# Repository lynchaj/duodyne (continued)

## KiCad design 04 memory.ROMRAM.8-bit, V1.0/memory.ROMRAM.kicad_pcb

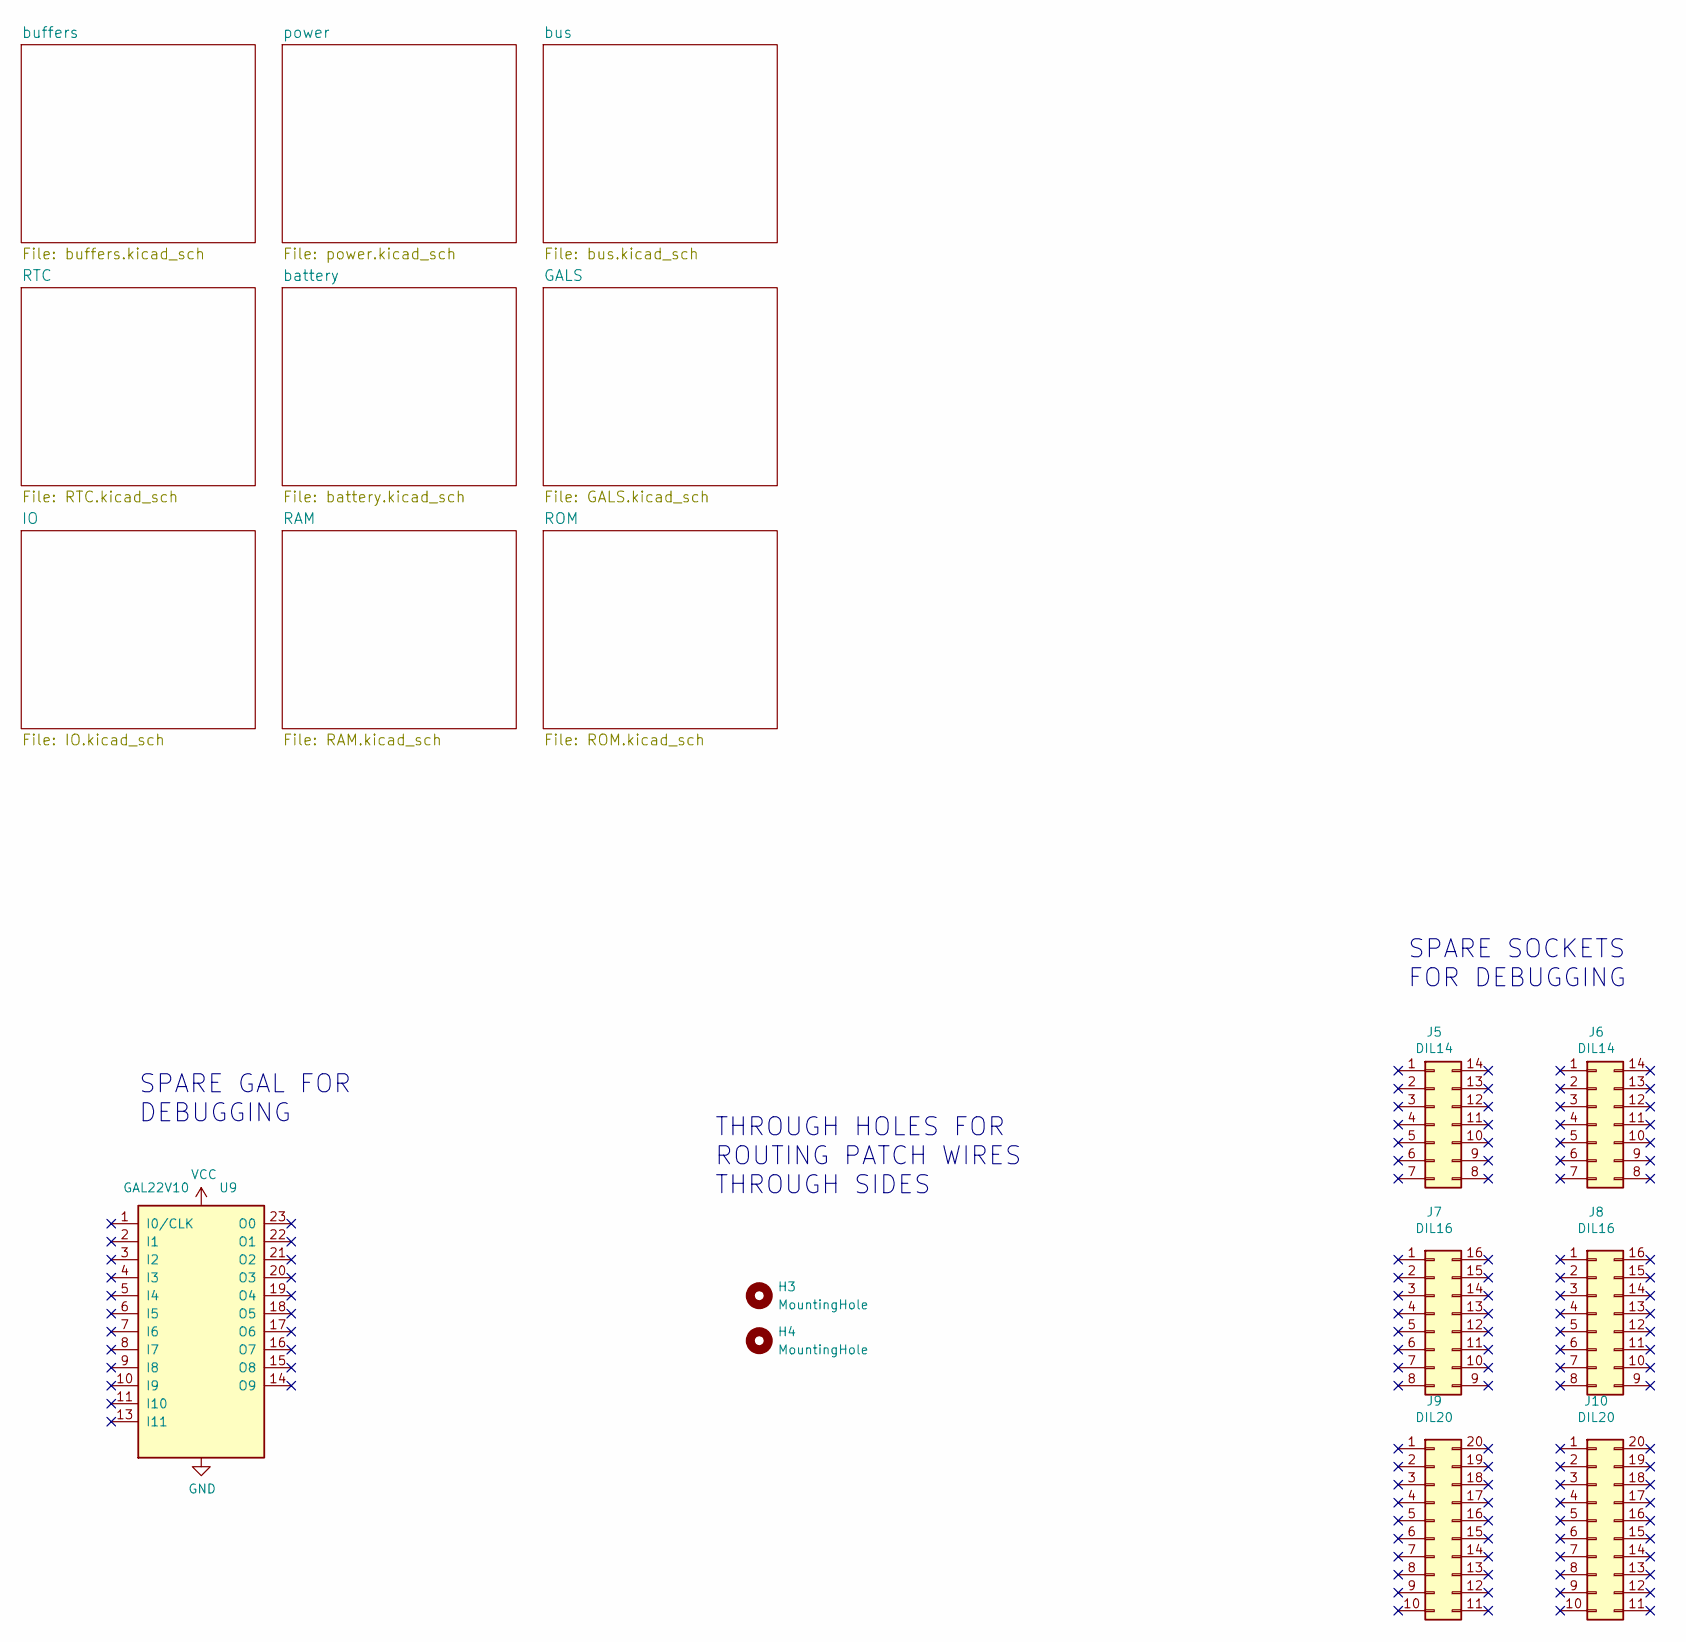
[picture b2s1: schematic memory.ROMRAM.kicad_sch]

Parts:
H3, H4: MountingHole; MountingHole_2.1mm
J5, J6: DIL14; DIP-14_W7.62mm
J7, J8: DIL16; DIP-16_W7.62mm
J9, J10: DIL20; DIP-20_W7.62mm
U9: GAL22V10; DIP-24_W7.62mm

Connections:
GND: U9.12 (GND); also elsewhere on the board
VCC: U9.24 (VCC); also elsewhere on the board

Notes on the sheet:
SPARE SOCKETS FOR DEBUGGING
SPARE GAL FOR DEBUGGING
THROUGH HOLES FOR ROUTING PATCH WIRES THROUGH SIDES

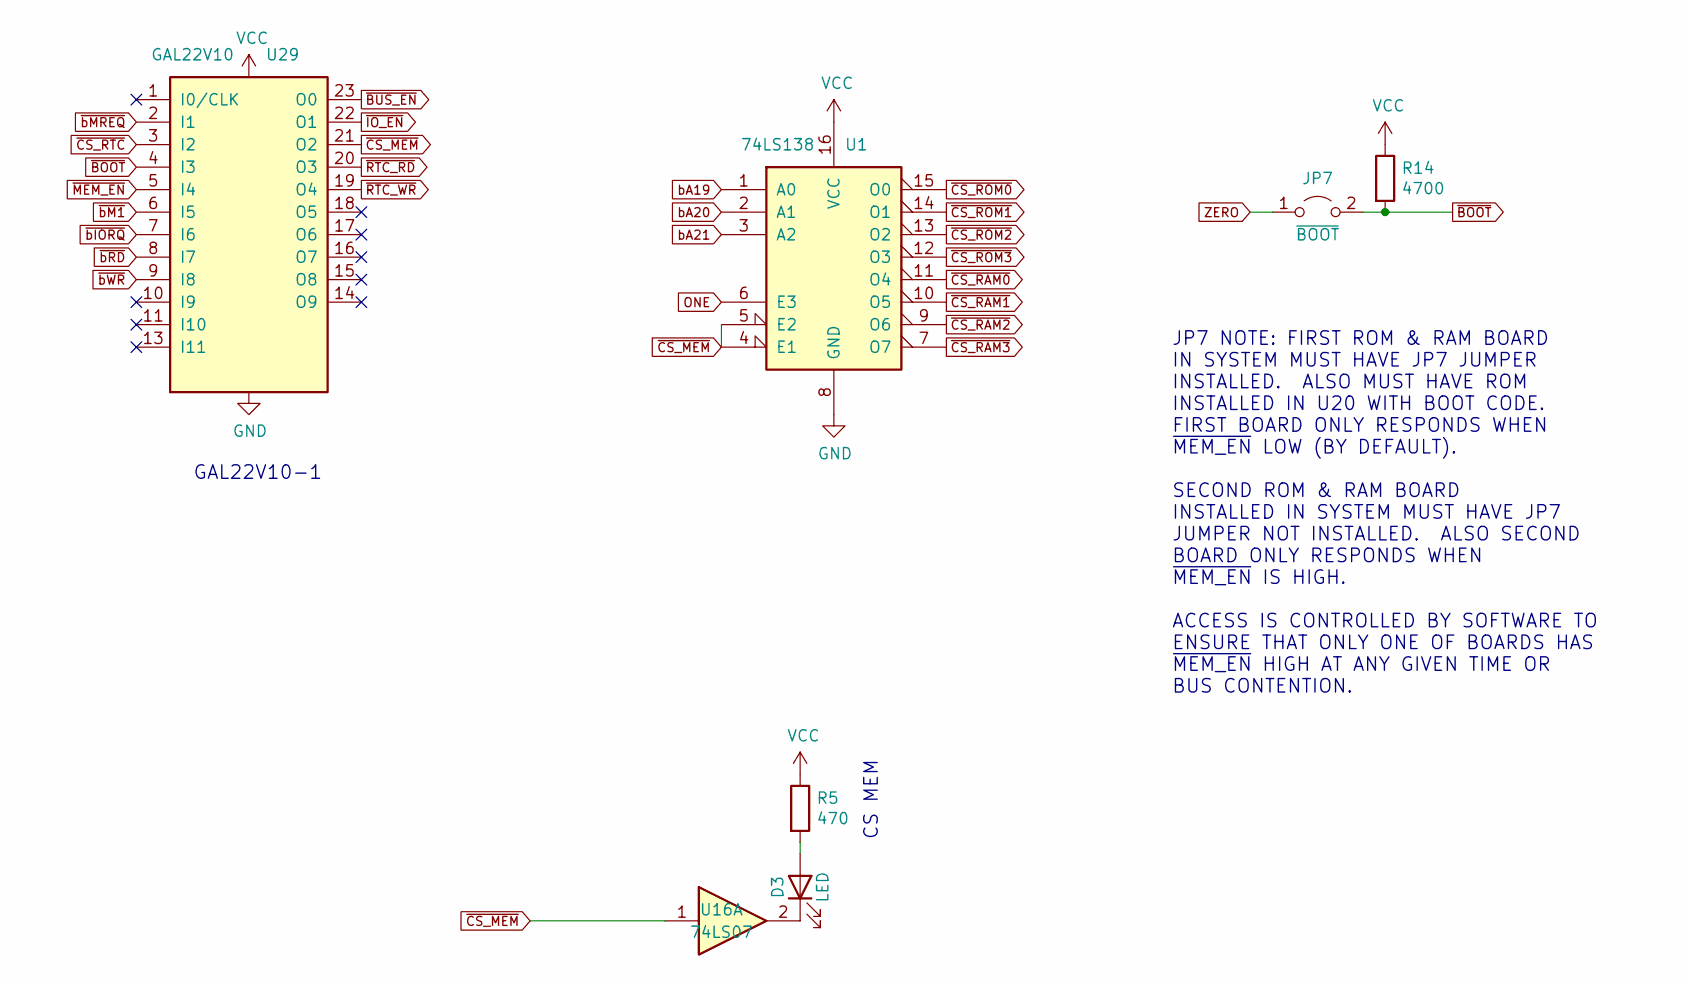
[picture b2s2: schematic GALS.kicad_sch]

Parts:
D3: LED; LED_D3.0mm_Horizontal_O3.81mm_Z2.0mm
JP7: ~{BOOT}; PinHeader_1x02_P2.54mm_Horizontal
R5: 470; R_Axial_DIN0207_L6.3mm_D2.5mm_P7.62mm_Horizontal
R14: 4700; R_Axial_DIN0207_L6.3mm_D2.5mm_P7.62mm_Horizontal
U1: 74LS138; DIP-16_W7.62mm
U16: 74LS07; DIP-14_W7.62mm
U29: GAL22V10; DIP-24_W7.62mm

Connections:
GND: U1.8 (GND), U29.12 (GND); also elsewhere on the board
unnamed: D3.1 (K), U16.2
unnamed: D3.2 (A), R5.2
ONE: U1.6 (E3); also elsewhere on the board
VCC: R5.1, R14.1, U1.16 (VCC), U29.24 (VCC); also elsewhere on the board
ZERO: JP7.1 (A); also elsewhere on the board
bA19: U1.1 (A0); also elsewhere on the board
bA20: U1.2 (A1); also elsewhere on the board
bA21: U1.3 (A2); also elsewhere on the board
~BOOT: JP7.2 (B), R14.2, U29.4 (I3)
~BUS_EN: U29.23 (O0); also elsewhere on the board
~CS_MEM: U1.4 (E1), U1.5 (E2), U16.1, U29.21 (O2)
~CS_RAM0: U1.11 (O4); also elsewhere on the board
~CS_RAM1: U1.10 (O5); also elsewhere on the board
~CS_RAM2: U1.9 (O6); also elsewhere on the board
~CS_RAM3: U1.7 (O7); also elsewhere on the board
~CS_ROM0: U1.15 (O0); also elsewhere on the board
~CS_ROM1: U1.14 (O1); also elsewhere on the board
~CS_ROM2: U1.13 (O2); also elsewhere on the board
~CS_ROM3: U1.12 (O3); also elsewhere on the board
~CS_RTC: U29.3 (I2); also elsewhere on the board
~IO_EN: U29.22 (O1); also elsewhere on the board
~MEM_EN: U29.5 (I4); also elsewhere on the board
~RTC_RD: U29.20 (O3); also elsewhere on the board
~RTC_WR: U29.19 (O4); also elsewhere on the board
~bIORQ: U29.7 (I6); also elsewhere on the board
~bM1: U29.6 (I5); also elsewhere on the board
~bMREQ: U29.2 (I1); also elsewhere on the board
~bRD: U29.8 (I7); also elsewhere on the board
~bWR: U29.9 (I8); also elsewhere on the board

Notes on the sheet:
GAL22V10-1
JP7 NOTE: FIRST ROM & RAM BOARD IN SYSTEM MUST HAVE JP7 JUMPER INSTALLED. ALSO MUST HAVE ROM INSTALLED IN U20 WITH BOOT CODE. FIRST BOARD ONLY RESPONDS WHEN ~{MEM_EN} LOW (BY DEFAULT). SECOND ROM & RAM BOARD INSTALLED IN SYSTEM MUST HAVE JP7 JUMPER NOT INSTALLED. ALSO SECOND BOARD ONLY RESPONDS WHE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
CS MEM

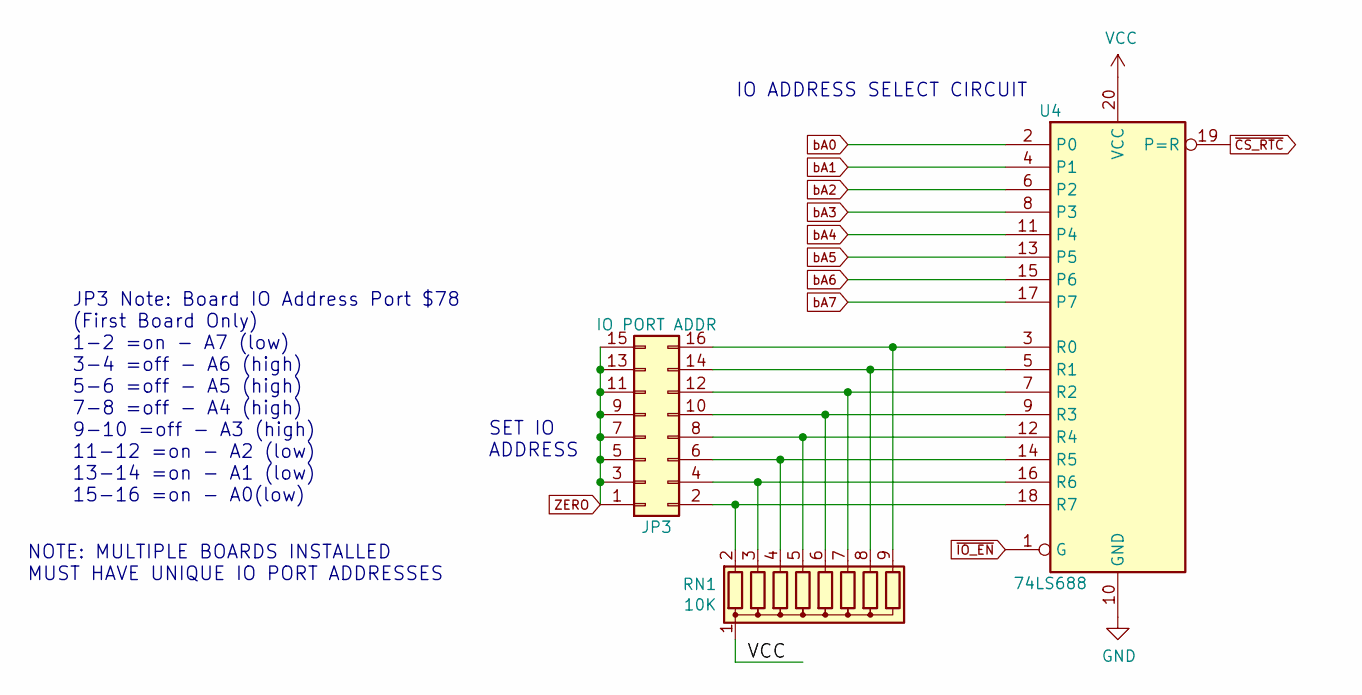
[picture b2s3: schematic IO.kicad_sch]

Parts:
JP3: IO PORT ADDR; PinHeader_2x08_P2.54mm_Vertical
RN1: 10K; R_Array_SIP9
U4: 74LS688; DIP-20_W7.62mm

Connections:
GND: U4.10 (GND); also elsewhere on the board
unnamed: JP3.2, RN1.2 (R1), U4.18 (R7)
unnamed: JP3.4, RN1.3 (R2), U4.16 (R6)
unnamed: JP3.6, RN1.4 (R3), U4.14 (R5)
unnamed: JP3.8, RN1.5 (R4), U4.12 (R4)
unnamed: JP3.10, RN1.6 (R5), U4.9 (R3)
unnamed: JP3.12, RN1.7 (R6), U4.7 (R2)
unnamed: JP3.14, RN1.8 (R7), U4.5 (R1)
unnamed: JP3.16, RN1.9 (R8), U4.3 (R0)
VCC: RN1.1 (common), U4.20 (VCC); also elsewhere on the board
ZERO: JP3.1, JP3.3, JP3.5, JP3.7, JP3.9, JP3.11, JP3.13, JP3.15; also elsewhere on the board
bA0: U4.2 (P0); also elsewhere on the board
bA1: U4.4 (P1); also elsewhere on the board
bA2: U4.6 (P2); also elsewhere on the board
bA3: U4.8 (P3); also elsewhere on the board
bA4: U4.11 (P4); also elsewhere on the board
bA5: U4.13 (P5); also elsewhere on the board
bA6: U4.15 (P6); also elsewhere on the board
bA7: U4.17 (P7); also elsewhere on the board
~CS_RTC: U4.19 (P=R); also elsewhere on the board
~IO_EN: U4.1 (G); also elsewhere on the board

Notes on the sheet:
JP3 Note: Board IO Address Port $78 (First Board Only) 1-2 =on - A7 (low) 3-4 =off - A6 (high) 5-6 =off - A5 (high) 7-8 =off - A4 (high) 9-10 =off - A3 (high) 11-12 =on - A2 (low) 13-14 =on - A1 (low) 15-16 =on - A0(low)
NOTE: MULTIPLE BOARDS INSTALLED MUST HAVE UNIQUE IO PORT ADDRESSES
IO ADDRESS SELECT CIRCUIT
SET IO ADDRESS

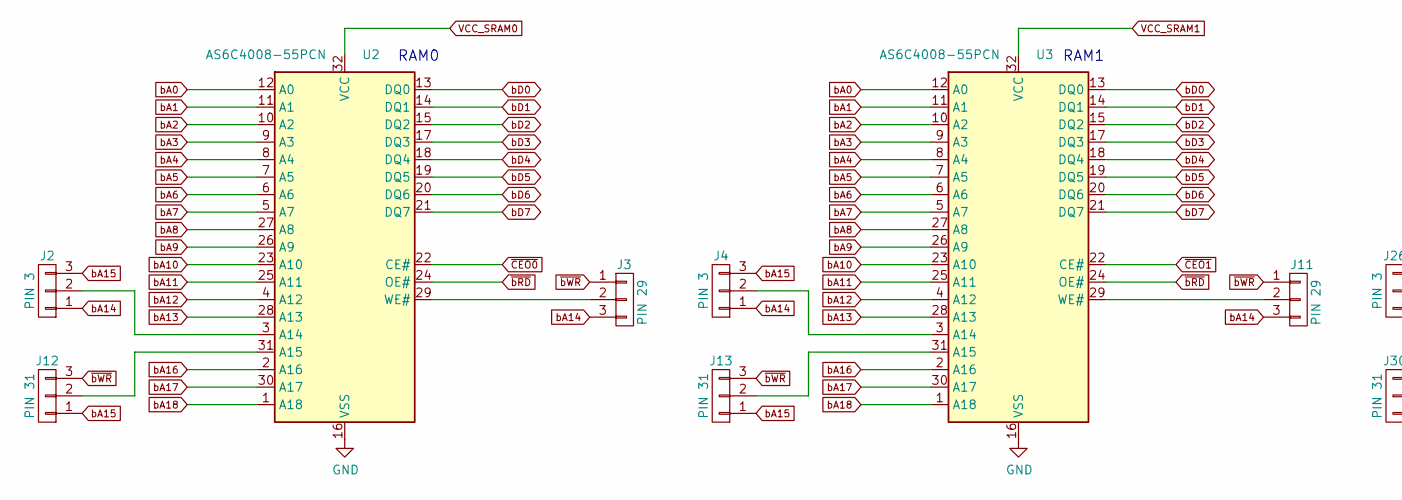
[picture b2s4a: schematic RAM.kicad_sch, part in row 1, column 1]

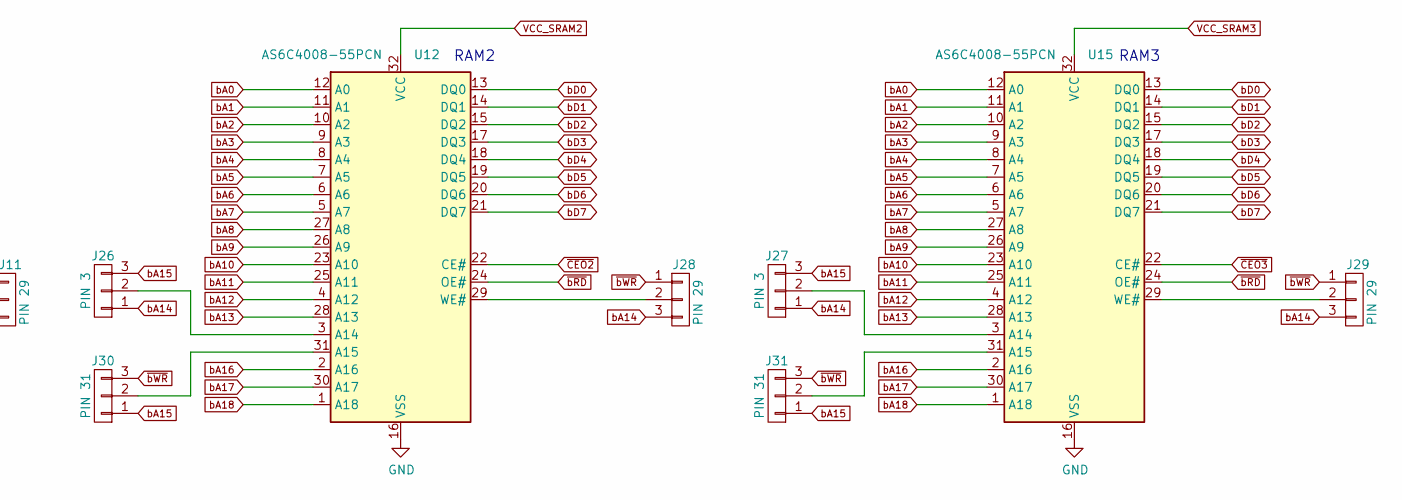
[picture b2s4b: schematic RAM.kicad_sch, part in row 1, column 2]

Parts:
J2, J4, J26, J27: PIN 3; PinHeader_1x03_P2.54mm_Vertical
J3, J11, J28, J29: PIN 29; PinHeader_1x03_P2.54mm_Vertical
J12, J13, J30, J31: PIN 31; PinHeader_1x03_P2.54mm_Vertical
U2, U3, U12, U15: AS6C4008-55PCN; DIP-32_W15.24mm

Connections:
GND: U2.16 (VSS), U3.16 (VSS), U12.16 (VSS), U15.16 (VSS); also elsewhere on the board
unnamed: J2.2, U2.3 (A14)
unnamed: J3.2, U2.29 (WE#)
unnamed: J4.2, U3.3 (A14)
unnamed: J11.2, U3.29 (WE#)
unnamed: J12.2, U2.31 (A15)
unnamed: J13.2, U3.31 (A15)
unnamed: J26.2, U12.3 (A14)
unnamed: J27.2, U15.3 (A14)
unnamed: J28.2, U12.29 (WE#)
unnamed: J29.2, U15.29 (WE#)
unnamed: J30.2, U12.31 (A15)
unnamed: J31.2, U15.31 (A15)
VCC_SRAM0: U2.32 (VCC); also elsewhere on the board
VCC_SRAM1: U3.32 (VCC); also elsewhere on the board
VCC_SRAM2: U12.32 (VCC); also elsewhere on the board
VCC_SRAM3: U15.32 (VCC); also elsewhere on the board
bA0: U2.12 (A0), U3.12 (A0), U12.12 (A0), U15.12 (A0); also elsewhere on the board
bA1: U2.11 (A1), U3.11 (A1), U12.11 (A1), U15.11 (A1); also elsewhere on the board
bA2: U2.10 (A2), U3.10 (A2), U12.10 (A2), U15.10 (A2); also elsewhere on the board
bA3: U2.9 (A3), U3.9 (A3), U12.9 (A3), U15.9 (A3); also elsewhere on the board
bA4: U2.8 (A4), U3.8 (A4), U12.8 (A4), U15.8 (A4); also elsewhere on the board
bA5: U2.7 (A5), U3.7 (A5), U12.7 (A5), U15.7 (A5); also elsewhere on the board
bA6: U2.6 (A6), U3.6 (A6), U12.6 (A6), U15.6 (A6); also elsewhere on the board
bA7: U2.5 (A7), U3.5 (A7), U12.5 (A7), U15.5 (A7); also elsewhere on the board
bA8: U2.27 (A8), U3.27 (A8), U12.27 (A8), U15.27 (A8); also elsewhere on the board
bA9: U2.26 (A9), U3.26 (A9), U12.26 (A9), U15.26 (A9); also elsewhere on the board
bA10: U2.23 (A10), U3.23 (A10), U12.23 (A10), U15.23 (A10); also elsewhere on the board
bA11: U2.25 (A11), U3.25 (A11), U12.25 (A11), U15.25 (A11); also elsewhere on the board
bA12: U2.4 (A12), U3.4 (A12), U12.4 (A12), U15.4 (A12); also elsewhere on the board
bA13: U2.28 (A13), U3.28 (A13), U12.28 (A13), U15.28 (A13); also elsewhere on the board
bA14: J2.1, J3.3, J4.1, J11.3, J26.1, J27.1, J28.3, J29.3; also elsewhere on the board
bA15: J2.3, J4.3, J12.1, J13.1, J26.3, J27.3, J30.1, J31.1; also elsewhere on the board
bA16: U2.2 (A16), U3.2 (A16), U12.2 (A16), U15.2 (A16); also elsewhere on the board
bA17: U2.30 (A17), U3.30 (A17), U12.30 (A17), U15.30 (A17); also elsewhere on the board
bA18: U2.1 (A18), U3.1 (A18), U12.1 (A18), U15.1 (A18); also elsewhere on the board
bD0: U2.13 (DQ0), U3.13 (DQ0), U12.13 (DQ0), U15.13 (DQ0); also elsewhere on the board
bD1: U2.14 (DQ1), U3.14 (DQ1), U12.14 (DQ1), U15.14 (DQ1); also elsewhere on the board
bD2: U2.15 (DQ2), U3.15 (DQ2), U12.15 (DQ2), U15.15 (DQ2); also elsewhere on the board
bD3: U2.17 (DQ3), U3.17 (DQ3), U12.17 (DQ3), U15.17 (DQ3); also elsewhere on the board
bD4: U2.18 (DQ4), U3.18 (DQ4), U12.18 (DQ4), U15.18 (DQ4); also elsewhere on the board
bD5: U2.19 (DQ5), U3.19 (DQ5), U12.19 (DQ5), U15.19 (DQ5); also elsewhere on the board
bD6: U2.20 (DQ6), U3.20 (DQ6), U12.20 (DQ6), U15.20 (DQ6); also elsewhere on the board
bD7: U2.21 (DQ7), U3.21 (DQ7), U12.21 (DQ7), U15.21 (DQ7); also elsewhere on the board
~CEO0: U2.22 (CE#); also elsewhere on the board
~CEO1: U3.22 (CE#); also elsewhere on the board
~CEO2: U12.22 (CE#); also elsewhere on the board
~CEO3: U15.22 (CE#); also elsewhere on the board
~bRD: U2.24 (OE#), U3.24 (OE#), U12.24 (OE#), U15.24 (OE#); also elsewhere on the board
~bWR: J3.1, J11.1, J12.3, J13.3, J28.1, J29.1, J30.3, J31.3; also elsewhere on the board

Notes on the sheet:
RAM1
RAM2
RAM3
RAM0

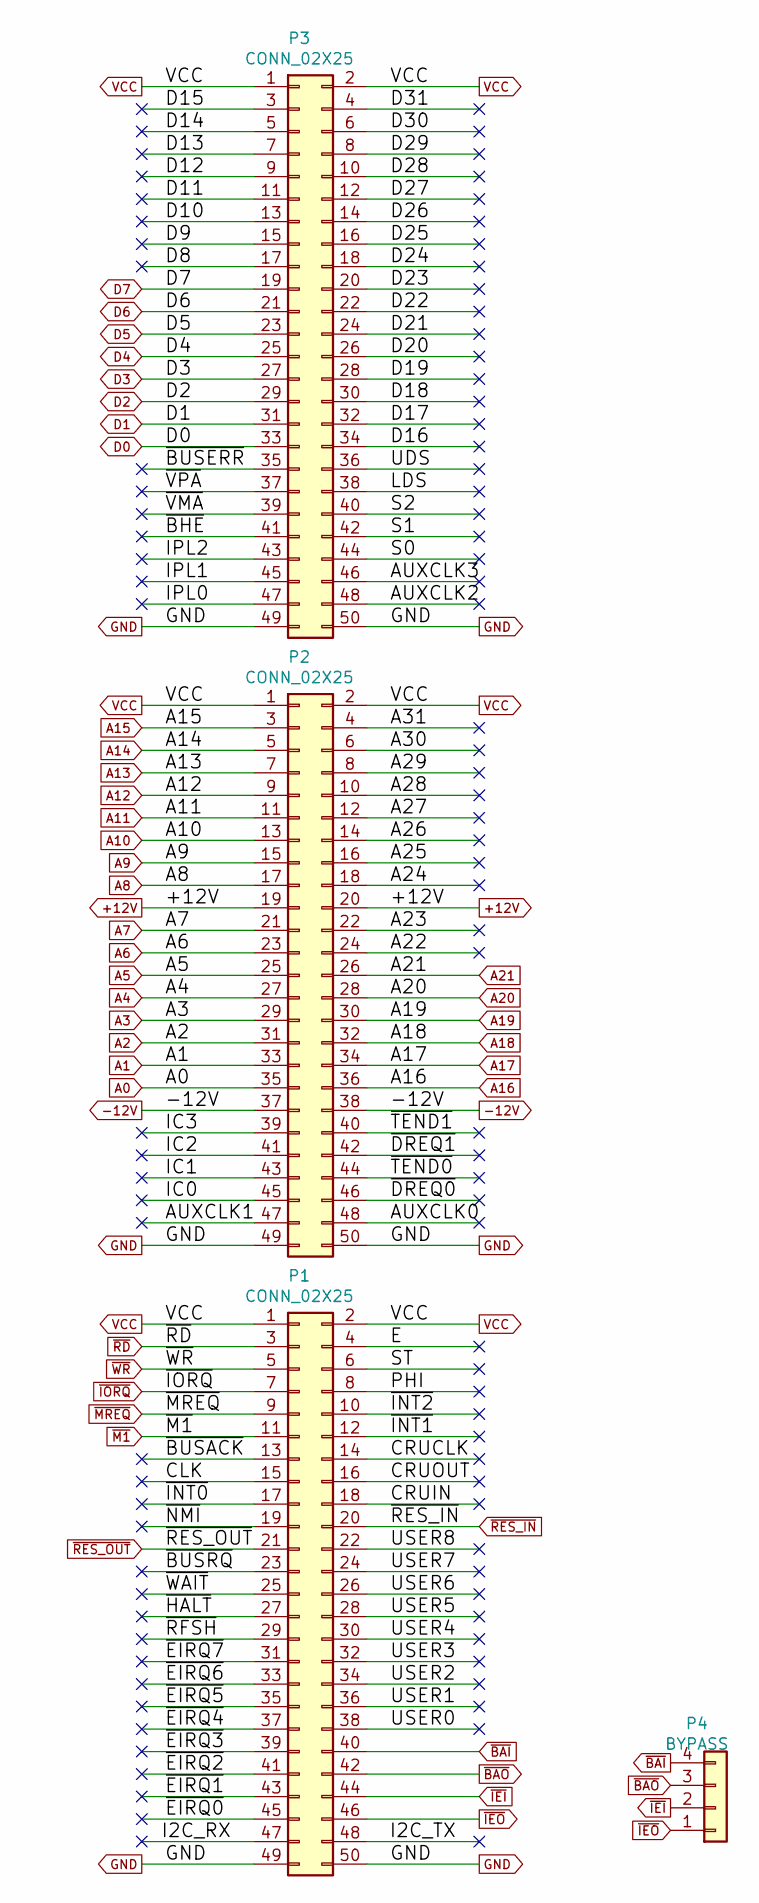
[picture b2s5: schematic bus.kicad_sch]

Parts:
P1, P2, P3: CONN_02X25; IDC-Header_2x25_P2.54mm_Horizontal
P4: BYPASS; PinHeader_1x04_P2.54mm_Vertical

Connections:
+12V: P2.19, P2.20
-12V: P2.37, P2.38
/bus/A22: P2.24
/bus/A23: P2.22
/bus/A24: P2.18
/bus/A25: P2.16
/bus/A26: P2.14
/bus/A27: P2.12
/bus/A28: P2.10
/bus/A29: P2.8
/bus/A30: P2.6
/bus/A31: P2.4
/bus/AUXCLK0: P2.48
/bus/AUXCLK1: P2.47
/bus/AUXCLK2: P3.48
/bus/AUXCLK3: P3.46
/bus/CLK: P1.15
/bus/CRUCLK: P1.14
/bus/CRUIN: P1.18
/bus/CRUOUT: P1.16
/bus/D8: P3.17
/bus/D9: P3.15
/bus/D10: P3.13
/bus/D11: P3.11
/bus/D12: P3.9
/bus/D13: P3.7
/bus/D14: P3.5
/bus/D15: P3.3
/bus/D16: P3.34
/bus/D17: P3.32
/bus/D18: P3.30
/bus/D19: P3.28
/bus/D20: P3.26
/bus/D21: P3.24
/bus/D22: P3.22
/bus/D23: P3.20
/bus/D24: P3.18
/bus/D25: P3.16
/bus/D26: P3.14
/bus/D27: P3.12
/bus/D28: P3.10
/bus/D29: P3.8
/bus/D30: P3.6
/bus/D31: P3.4
/bus/E: P1.4
/bus/IC0: P2.45
/bus/IC1: P2.43
/bus/IC2: P2.41
/bus/IC3: P2.39
/bus/IPL0: P3.47
/bus/IPL1: P3.45
/bus/IPL2: P3.43
/bus/LDS: P3.38
/bus/PHI: P1.8
/bus/S0: P3.44
/bus/S1: P3.42
/bus/S2: P3.40
/bus/ST: P1.6
/bus/UDS: P3.36
/bus/USER0: P1.38
/bus/USER1: P1.36
/bus/USER2: P1.34
/bus/USER3: P1.32
/bus/USER4: P1.30
/bus/USER5: P1.28
/bus/USER6: P1.26
/bus/USER7: P1.24
/bus/USER8: P1.22
/bus/~BHE: P3.41
/bus/~BUSACK: P1.13
/bus/~BUSERR: P3.35
/bus/~BUSRQ: P1.23
/bus/~DREQ0: P2.46
/bus/~DREQ1: P2.42
/bus/~EIRQ0: P1.45
/bus/~EIRQ1: P1.43
/bus/~EIRQ2: P1.41
/bus/~EIRQ3: P1.39
/bus/~EIRQ4: P1.37
/bus/~EIRQ5: P1.35
/bus/~EIRQ6: P1.33
/bus/~EIRQ7: P1.31
/bus/~HALT: P1.27
/bus/~INT0: P1.17
/bus/~INT1: P1.12
/bus/~INT2: P1.10
/bus/~NMI: P1.19
/bus/~RFSH: P1.29
/bus/~TEND0: P2.44
/bus/~TEND1: P2.40
/bus/~VMA: P3.39
/bus/~VPA: P3.37
/bus/~WAIT: P1.25
A0: P2.35; also elsewhere on the board
A1: P2.33; also elsewhere on the board
A2: P2.31; also elsewhere on the board
A3: P2.29; also elsewhere on the board
A4: P2.27; also elsewhere on the board
A5: P2.25; also elsewhere on the board
A6: P2.23; also elsewhere on the board
A7: P2.21; also elsewhere on the board
A8: P2.17; also elsewhere on the board
A9: P2.15; also elsewhere on the board
A10: P2.13; also elsewhere on the board
A11: P2.11; also elsewhere on the board
A12: P2.9; also elsewhere on the board
A13: P2.7; also elsewhere on the board
A14: P2.5; also elsewhere on the board
A15: P2.3; also elsewhere on the board
A16: P2.36; also elsewhere on the board
A17: P2.34; also elsewhere on the board
A18: P2.32; also elsewhere on the board
A19: P2.30; also elsewhere on the board
A20: P2.28; also elsewhere on the board
A21: P2.26; also elsewhere on the board
D0: P3.33; also elsewhere on the board
D1: P3.31; also elsewhere on the board
D2: P3.29; also elsewhere on the board
D3: P3.27; also elsewhere on the board
D4: P3.25; also elsewhere on the board
D5: P3.23; also elsewhere on the board
D6: P3.21; also elsewhere on the board
D7: P3.19; also elsewhere on the board
GND: P1.49, P1.50, P2.49, P2.50, P3.49, P3.50; also elsewhere on the board
I2C_SCL: P1.47; also elsewhere on the board
I2C_SDA: P1.48; also elsewhere on the board
VCC: P1.1, P1.2, P2.1, P2.2, P3.1, P3.2; also elsewhere on the board
~BAI: P1.40, P4.4
~BAO: P1.42, P4.3
~IEI: P1.44, P4.2
~IEO: P1.46, P4.1
~IORQ: P1.7; also elsewhere on the board
~M1: P1.11; also elsewhere on the board
~MREQ: P1.9; also elsewhere on the board
~RD: P1.3; also elsewhere on the board
~RES_IN: P1.20; also elsewhere on the board
~RES_OUT: P1.21; also elsewhere on the board
~WR: P1.5; also elsewhere on the board

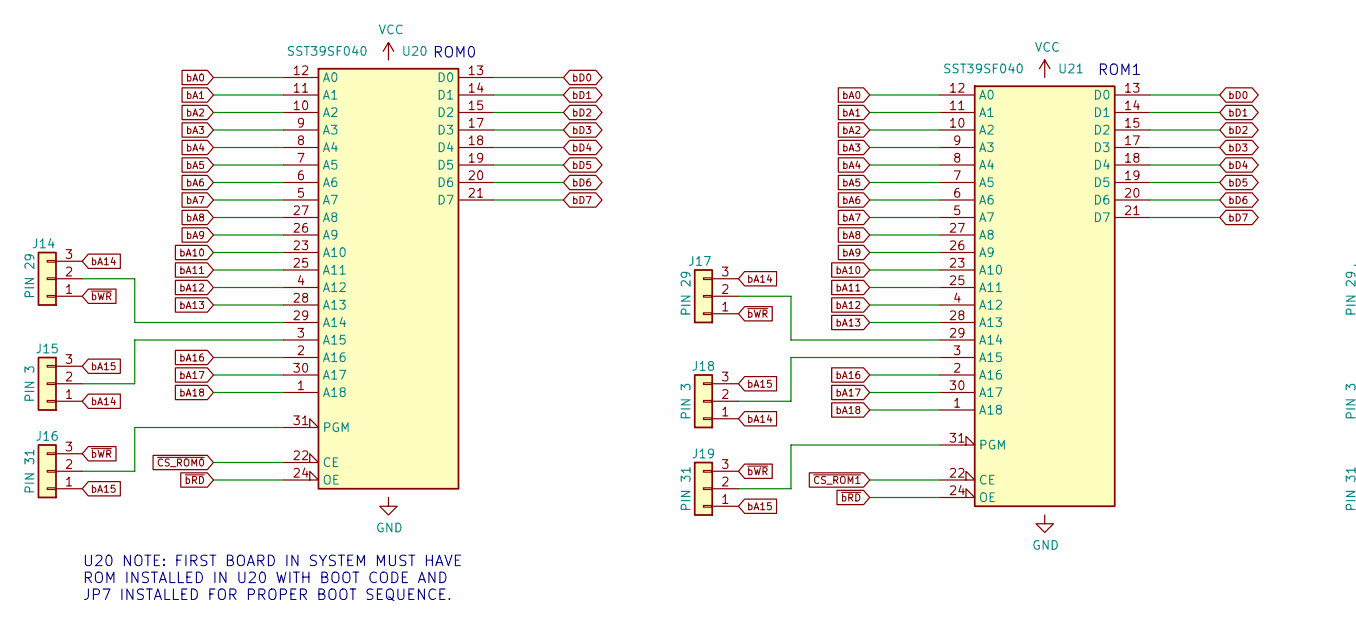
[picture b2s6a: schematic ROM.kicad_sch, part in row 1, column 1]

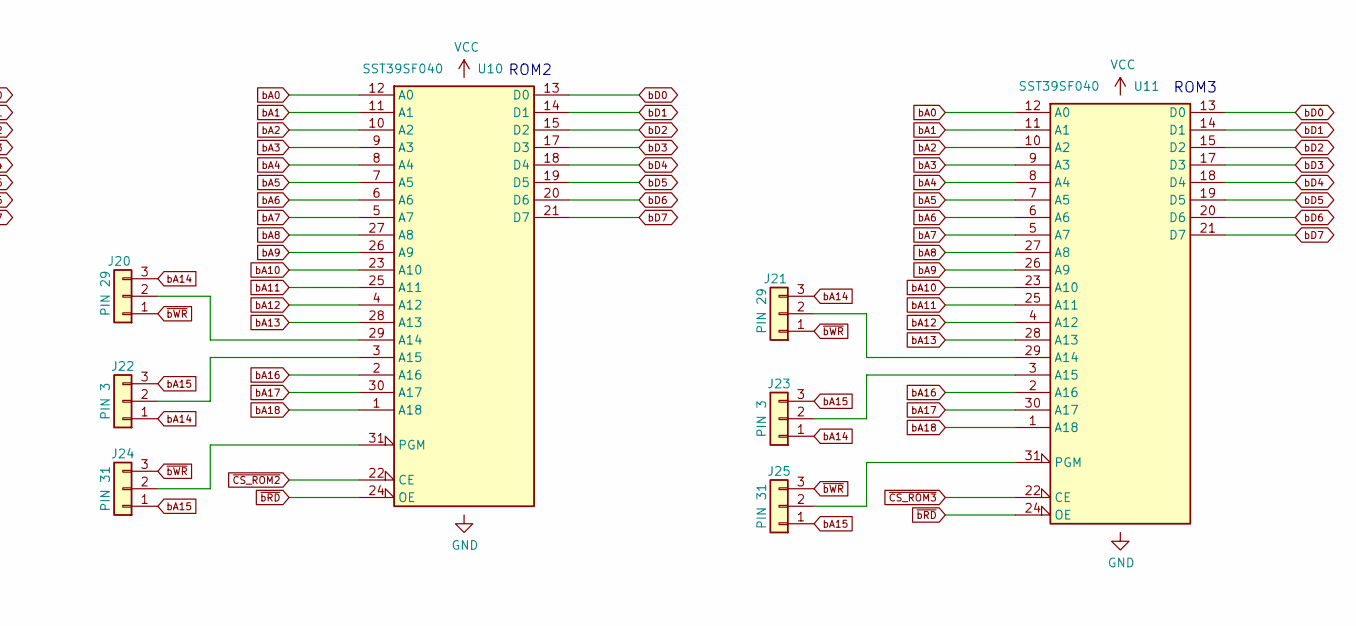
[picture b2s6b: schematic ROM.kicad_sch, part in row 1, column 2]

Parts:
J14, J17, J20, J21: PIN 29; PinHeader_1x03_P2.54mm_Vertical
J15, J18, J22, J23: PIN 3; PinHeader_1x03_P2.54mm_Vertical
J16, J19, J24, J25: PIN 31; PinHeader_1x03_P2.54mm_Vertical
U10, U11, U20, U21: SST39SF040; DIP-32_W15.24mm

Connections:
GND: U10.16 (GND), U11.16 (GND), U20.16 (GND), U21.16 (GND); also elsewhere on the board
unnamed: J14.2, U20.29 (A14)
unnamed: J15.2, U20.3 (A15)
unnamed: J16.2, U20.31 (PGM)
unnamed: J17.2, U21.29 (A14)
unnamed: J18.2, U21.3 (A15)
unnamed: J19.2, U21.31 (PGM)
unnamed: J20.2, U10.29 (A14)
unnamed: J21.2, U11.29 (A14)
unnamed: J22.2, U10.3 (A15)
unnamed: J23.2, U11.3 (A15)
unnamed: J24.2, U10.31 (PGM)
unnamed: J25.2, U11.31 (PGM)
VCC: U10.32 (VCC), U11.32 (VCC), U20.32 (VCC), U21.32 (VCC); also elsewhere on the board
bA0: U10.12 (A0), U11.12 (A0), U20.12 (A0), U21.12 (A0); also elsewhere on the board
bA1: U10.11 (A1), U11.11 (A1), U20.11 (A1), U21.11 (A1); also elsewhere on the board
bA2: U10.10 (A2), U11.10 (A2), U20.10 (A2), U21.10 (A2); also elsewhere on the board
bA3: U10.9 (A3), U11.9 (A3), U20.9 (A3), U21.9 (A3); also elsewhere on the board
bA4: U10.8 (A4), U11.8 (A4), U20.8 (A4), U21.8 (A4); also elsewhere on the board
bA5: U10.7 (A5), U11.7 (A5), U20.7 (A5), U21.7 (A5); also elsewhere on the board
bA6: U10.6 (A6), U11.6 (A6), U20.6 (A6), U21.6 (A6); also elsewhere on the board
bA7: U10.5 (A7), U11.5 (A7), U20.5 (A7), U21.5 (A7); also elsewhere on the board
bA8: U10.27 (A8), U11.27 (A8), U20.27 (A8), U21.27 (A8); also elsewhere on the board
bA9: U10.26 (A9), U11.26 (A9), U20.26 (A9), U21.26 (A9); also elsewhere on the board
bA10: U10.23 (A10), U11.23 (A10), U20.23 (A10), U21.23 (A10); also elsewhere on the board
bA11: U10.25 (A11), U11.25 (A11), U20.25 (A11), U21.25 (A11); also elsewhere on the board
bA12: U10.4 (A12), U11.4 (A12), U20.4 (A12), U21.4 (A12); also elsewhere on the board
bA13: U10.28 (A13), U11.28 (A13), U20.28 (A13), U21.28 (A13); also elsewhere on the board
bA14: J14.3, J15.1, J17.3, J18.1, J20.3, J21.3, J22.1, J23.1; also elsewhere on the board
bA15: J15.3, J16.1, J18.3, J19.1, J22.3, J23.3, J24.1, J25.1; also elsewhere on the board
bA16: U10.2 (A16), U11.2 (A16), U20.2 (A16), U21.2 (A16); also elsewhere on the board
bA17: U10.30 (A17), U11.30 (A17), U20.30 (A17), U21.30 (A17); also elsewhere on the board
bA18: U10.1 (A18), U11.1 (A18), U20.1 (A18), U21.1 (A18); also elsewhere on the board
bD0: U10.13 (D0), U11.13 (D0), U20.13 (D0), U21.13 (D0); also elsewhere on the board
bD1: U10.14 (D1), U11.14 (D1), U20.14 (D1), U21.14 (D1); also elsewhere on the board
bD2: U10.15 (D2), U11.15 (D2), U20.15 (D2), U21.15 (D2); also elsewhere on the board
bD3: U10.17 (D3), U11.17 (D3), U20.17 (D3), U21.17 (D3); also elsewhere on the board
bD4: U10.18 (D4), U11.18 (D4), U20.18 (D4), U21.18 (D4); also elsewhere on the board
bD5: U10.19 (D5), U11.19 (D5), U20.19 (D5), U21.19 (D5); also elsewhere on the board
bD6: U10.20 (D6), U11.20 (D6), U20.20 (D6), U21.20 (D6); also elsewhere on the board
bD7: U10.21 (D7), U11.21 (D7), U20.21 (D7), U21.21 (D7); also elsewhere on the board
~CS_ROM0: U20.22 (CE); also elsewhere on the board
~CS_ROM1: U21.22 (CE); also elsewhere on the board
~CS_ROM2: U10.22 (CE); also elsewhere on the board
~CS_ROM3: U11.22 (CE); also elsewhere on the board
~bRD: U10.24 (OE), U11.24 (OE), U20.24 (OE), U21.24 (OE); also elsewhere on the board
~bWR: J14.1, J16.3, J17.1, J19.3, J20.1, J21.1, J24.3, J25.3; also elsewhere on the board

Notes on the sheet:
ROM3
ROM1
ROM0
ROM2
U20 NOTE: FIRST BOARD IN SYSTEM MUST HAVE ROM INSTALLED IN U20 WITH BOOT CODE AND JP7 INSTALLED FOR PROPER BOOT SEQUENCE.

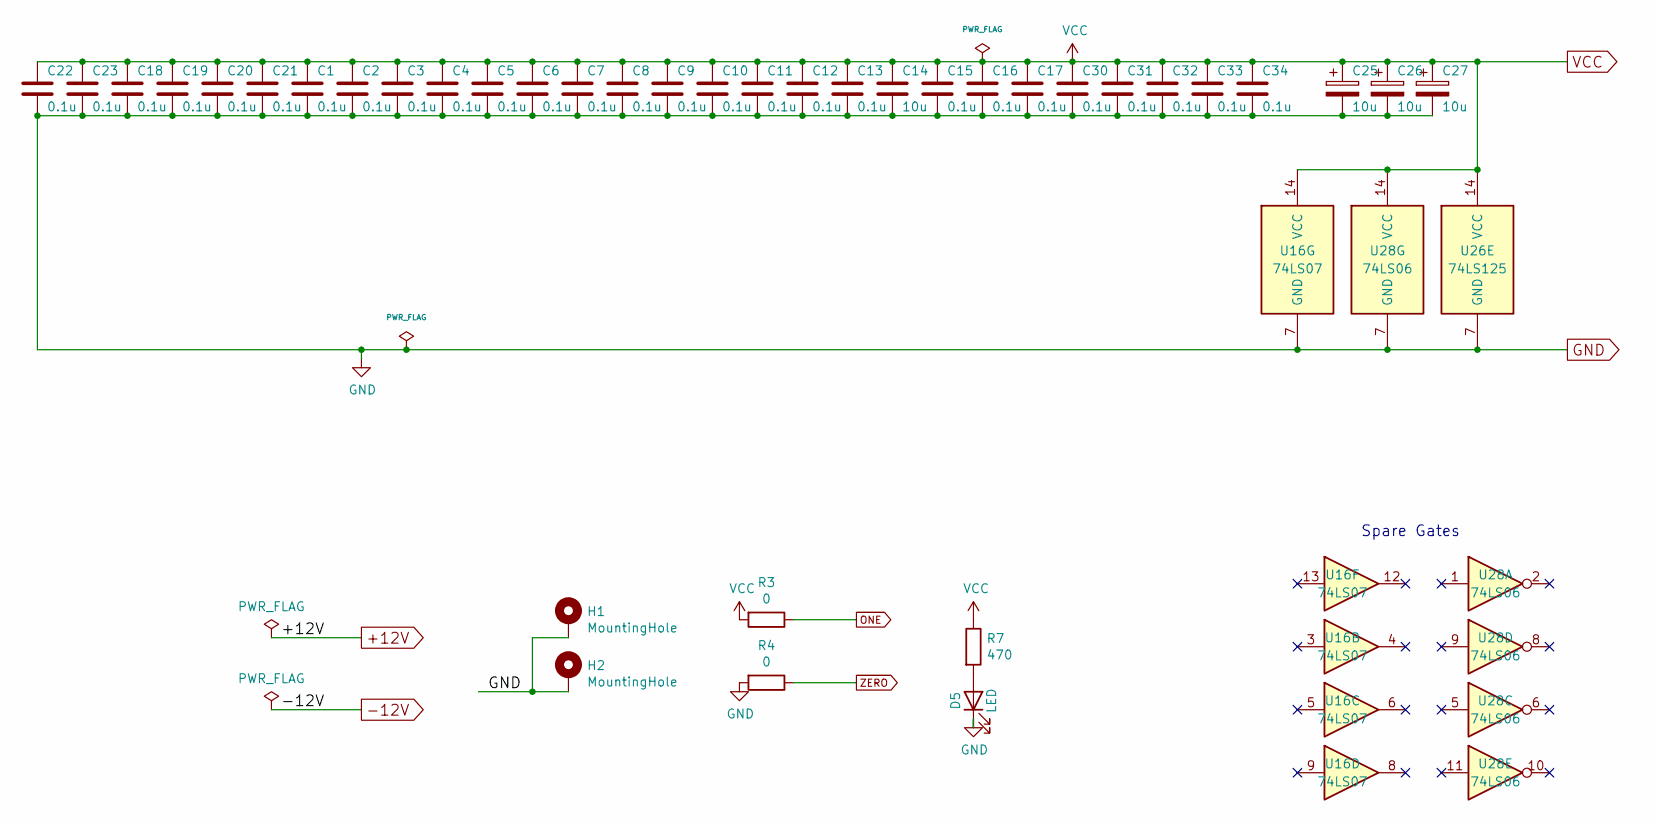
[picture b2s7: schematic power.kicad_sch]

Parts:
C1, C2, C3, C4, C5, C6, C7, C8, C9, C10, C11, C12, C13, C15, C16, C17, C18, C19, C20, C21, C22, C23, C30, C31, C32, C33, C34: 0.1u; C_Disc_D5.0mm_W2.5mm_P5.00mm
C14, C25, C26, C27: 10u; CP_Radial_D5.0mm_P2.50mm
D5: LED; LED_D3.0mm_Horizontal_O3.81mm_Z2.0mm
H1, H2: MountingHole; MountingHole_3.2mm_M3_Pad
R3, R4: 0; R_Axial_DIN0207_L6.3mm_D2.5mm_P7.62mm_Horizontal
R7: 470; R_Axial_DIN0207_L6.3mm_D2.5mm_P7.62mm_Horizontal
U16: 74LS07; DIP-14_W7.62mm
U26: 74LS125; DIP-14_W7.62mm
U28: 74LS06; DIP-14_W7.62mm

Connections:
GND: C1.2, C2.2, C3.2, C4.2, C5.2, C6.2, C7.2, C8.2, C9.2, C10.2, C11.2, C12.2, C13.2, C14.2, C15.2, C16.2, C17.2, C18.2, C19.2, C20.2, C21.2, C22.2, C23.2, C25.2, C26.2, C27.2, C30.2, C31.2, C32.2, C33.2, C34.2, D5.1 (K), H1.1, H2.1, R4.2, U16.7 (GND), U26.7 (GND), U28.7 (GND); also elsewhere on the board
unnamed: D5.2 (A), R7.2
VCC: C1.1, C2.1, C3.1, C4.1, C5.1, C6.1, C7.1, C8.1, C9.1, C10.1, C11.1, C12.1, C13.1, C14.1, C15.1, C16.1, C17.1, C18.1, C19.1, C20.1, C21.1, C22.1, C23.1, C25.1, C26.1, C27.1, C30.1, C31.1, C32.1, C33.1, C34.1, R3.2, R7.1, U16.14 (VCC), U26.14 (VCC), U28.14 (VCC); also elsewhere on the board

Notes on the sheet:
Spare Gates
